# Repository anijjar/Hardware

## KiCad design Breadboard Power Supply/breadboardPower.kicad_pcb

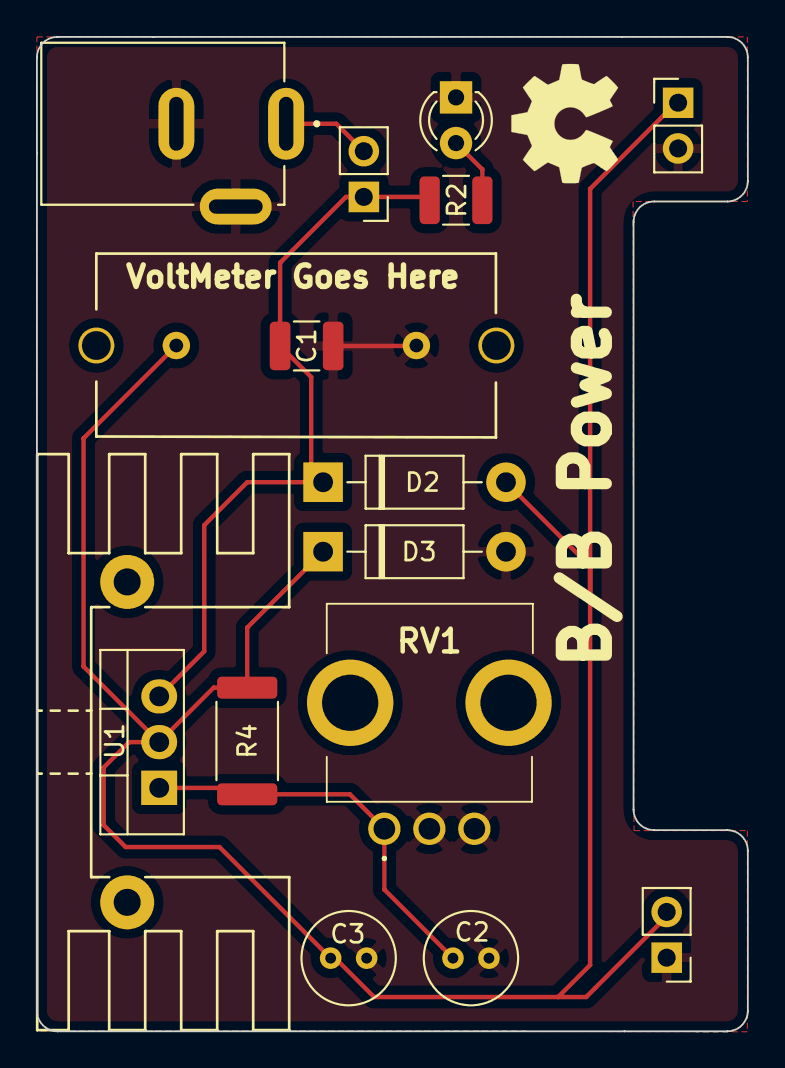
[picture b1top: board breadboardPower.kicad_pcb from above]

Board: 2 copper layers, 39.5 x 55.2 mm, 16 parts (0 on the bottom side), 6 nets.

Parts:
C1: 10u; C_1210_3225Metric
C2: 0F; C_Radial_D5.0mm_H7.0mm_P2.00mm
C3: 100u; C_Radial_D5.0mm_H7.0mm_P2.00mm
D1: LED; LED_D3.0mm_Clear
D2, D3: 1N4002; D_DO-41_SOD81_P10.16mm_Horizontal
HS1: Heatsink; Heatsink_Stonecold_HS-132_32x14mm_2xFixation1.5mm
J1: CON-SOCJ-2155; GRAVITECH_CON-SOCJ-2155
J2, J3: Conn_01x02; PinHeader_1x02_P2.54mm_Vertical
MES1: Voltmeter_DC; PRT-14313
R1: 0; PinHeader_1x02_P2.54mm_Vertical
R2: 1k; R_1210_3225Metric
R4: 250; R_2512_6332Metric
RV1: PTV09A-4020F-B202; PTV09A4020FB503
U1: TLV1117-ADJ; TO-220-3_Vertical

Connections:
GND: C1.2, C2.2, C3.2, D1.1, D3.2, J1.2, J1.3, J2.1, J3.2, MES1.1, RV1.2, RV1.3
unnamed: C1.1, D2.1, R1.1, R2.1, U1.3
unnamed: C2.1, R4.2, RV1.1, U1.1
unnamed: C3.1, D2.2, D3.1, J2.2, J3.1, MES1.2, R4.1, U1.2
unnamed: D1.2, R2.2
unnamed: J1.1, R1.2

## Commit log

2023-08-28 fixed Folder
2023-08-30 linked Master Repo into ESC
